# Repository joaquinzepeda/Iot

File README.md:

# Iot
Repositorio códigos curso Análisis y Diseño de Sistemas basados en Internet de las Cosas (IoT).

## Integrantes 
Ricardo Garcia, FCFM.  
Benjamín Irarrazabal, FCFM.  
Joaquín Zepeda, FCFM.  

# Diseño PCB

Se diseño la siguiente placa PCB para un sistema de regadio automático.

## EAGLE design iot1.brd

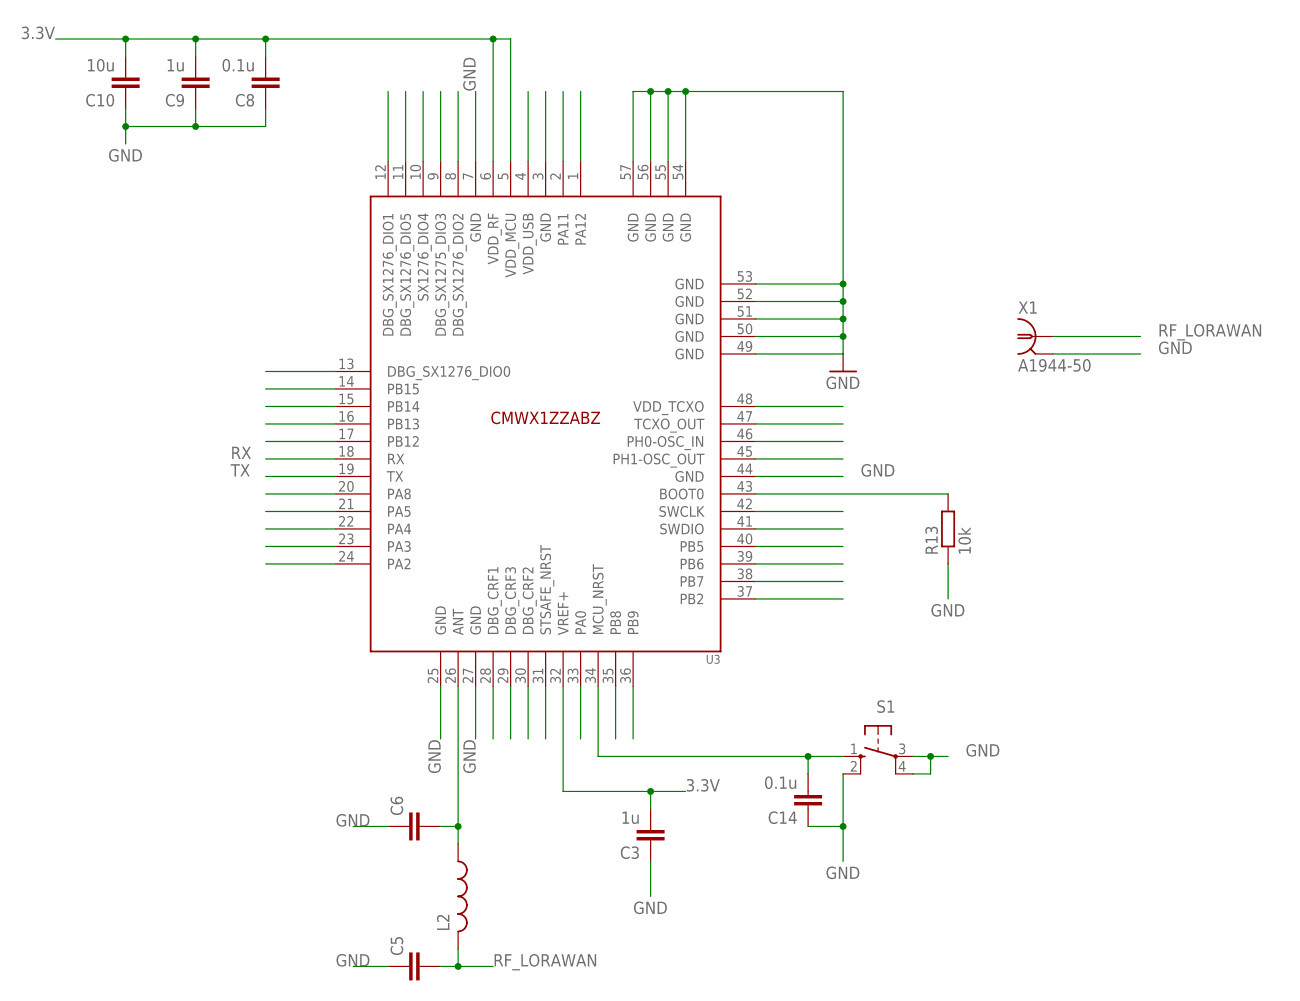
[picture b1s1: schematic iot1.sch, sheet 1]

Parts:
C3, C9: 1u; C050-025X075
C5, C6: C-EU050-025X075; C050-025X075
C8, C14: 0.1u; C050-025X075
C10: 10u; C050-025X075
L2: L-US0207/7; 0207/7
R13: 10k; 0204/5
S1: 10-XX; B3F-10XX
U3: CMWX1ZZABZ
X1: A1944-50; A1944

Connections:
3.3V: C3.2, C8.2, C9.2, C10.2, U3.5 (VDD_MCU), U3.6 (VDD_RF), U3.32 (VREF+); also elsewhere on the board
GND: C3.1, C5.1, C6.1, C8.1, C9.1, C10.1, C14.1, R13.1, S1.2 (S1), S1.3, S1.4 (P1), U3.7 (GND), U3.25 (GND), U3.27 (GND), U3.44 (GND), U3.49 (GND), U3.50 (GND), U3.51 (GND), U3.52 (GND), U3.53 (GND), U3.54 (GND), U3.55 (GND), U3.56 (GND), U3.57 (GND), X1.2, X1.3 (2), X1.4 (2), X1.5 (2); also elsewhere on the board
unnamed: C6.2, L2.1, U3.26 (ANT)
unnamed: C14.2, S1.1 (S), U3.34 (MCU_NRST)
unnamed: R13.2, U3.43 (BOOT0)
RF_LORAWAN: C5.2, L2.2, X1.1
RX: U3.18 (RX); also elsewhere on the board
TX: U3.19 (TX); also elsewhere on the board

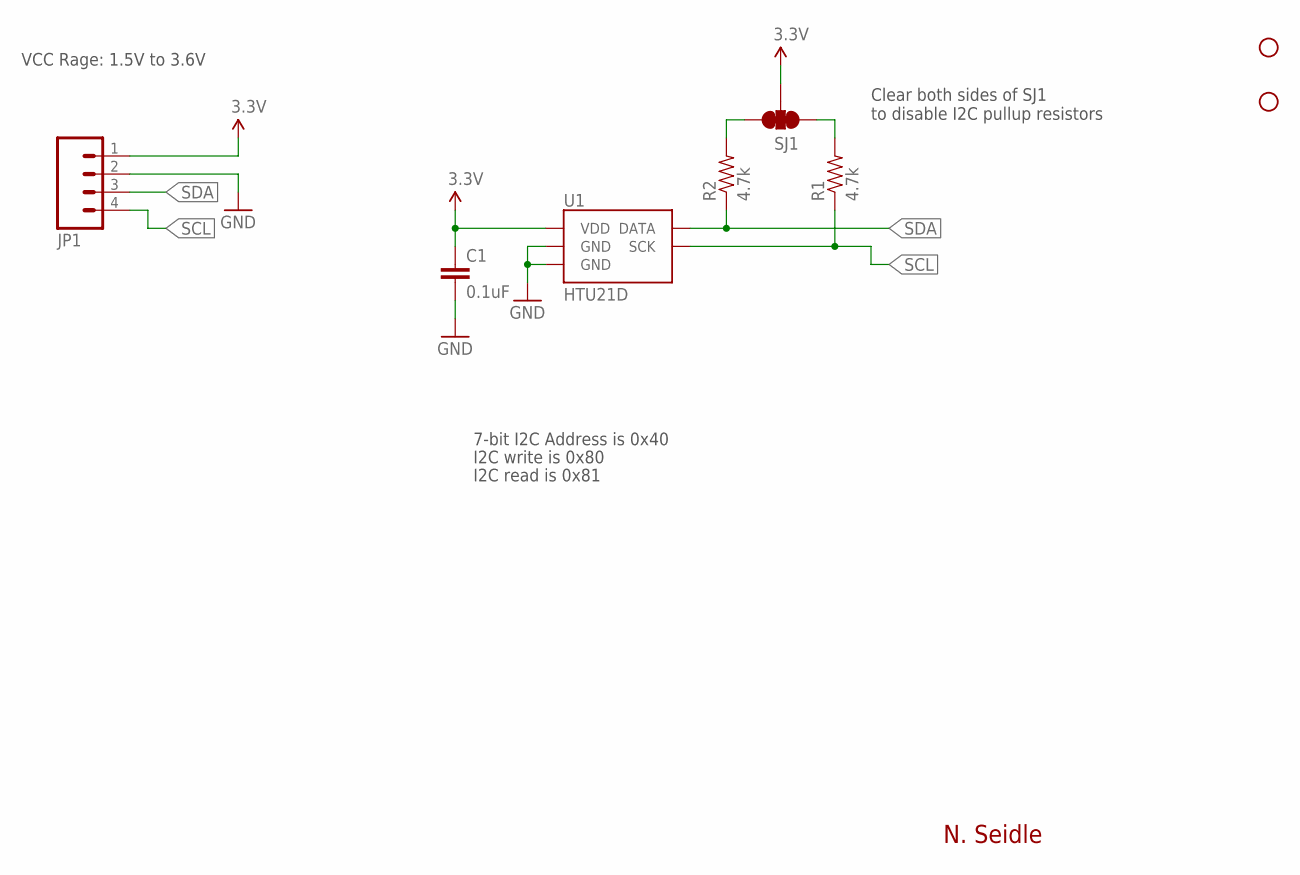
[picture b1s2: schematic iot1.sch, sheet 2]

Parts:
C1: 0.1uF; 0603-CAP
JP1: M04PTH; 1X04
R1, R2: 4.7k; 0603-RES
SJ1: SOLDERJUMPER_2WAYPASTE1&2&3; SJ_3_PASTE1&2&3
STANDOFF1, STANDOFF3: STAND-OFF
U1: HTU21D

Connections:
3.3V: C1.1, JP1.1, SJ1.2, U1.VDD; also elsewhere on the board
GND: C1.2, JP1.2, U1.7 (GND), U1.GND; also elsewhere on the board
unnamed: R2.2, SJ1.3
unnamed: R1.2, SJ1.1
SCL: JP1.4, R1.1, U1.SCK; also elsewhere on the board
SDA: JP1.3, R2.1, U1.DATA; also elsewhere on the board

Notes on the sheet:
N. Seidle
Clear both sides of SJ1 to disable I2C pullup resistors
VCC Rage: 1.5V to 3.6V
7-bit I2C Address is 0x40
I2C write is 0x80
I2C read is 0x81

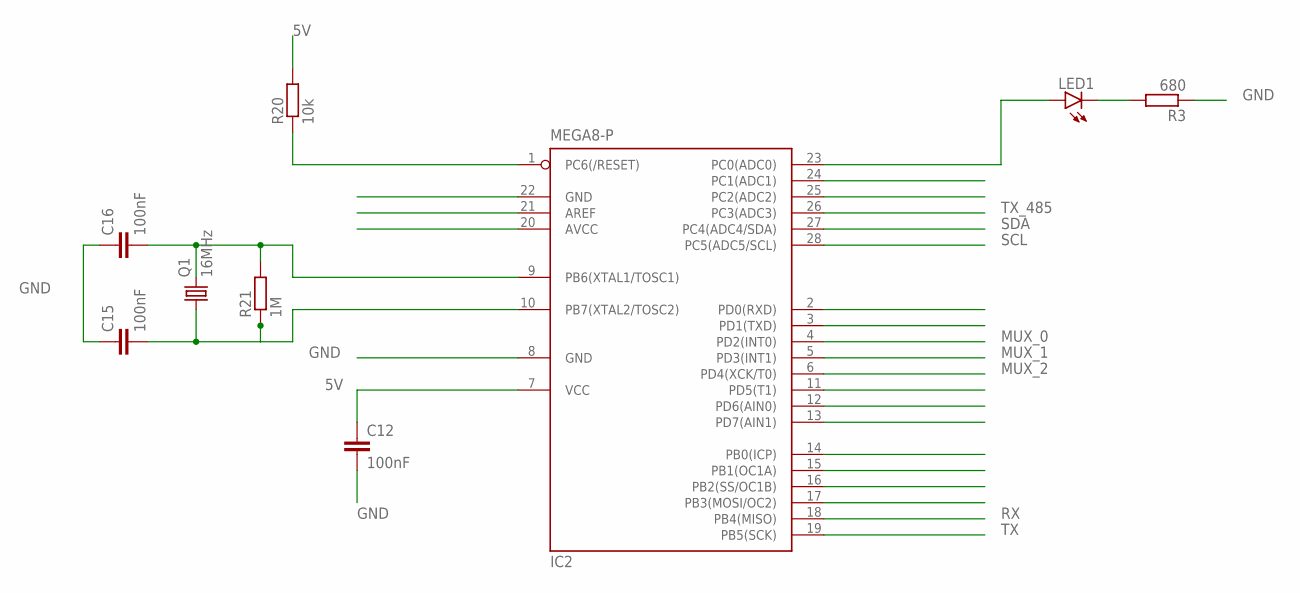
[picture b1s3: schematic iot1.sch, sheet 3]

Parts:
C12, C15, C16: 100nF; C050-025X075
IC2: MEGA8-P; DIL28-3
LED1: LED3MM
Q1: 16MHz; HC18U-V
R3: 680; 0207/10
R20: 10k; 0204/7
R21: 1M; 0204/7

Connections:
5V: C12.1, IC2.7 (VCC), R20.2; also elsewhere on the board
GND: C12.2, C15.1, C16.1, IC2.8 (GND), R3.1; also elsewhere on the board
MUX_0: IC2.4 (PD2(INT0)); also elsewhere on the board
MUX_1: IC2.5 (PD3(INT1)); also elsewhere on the board
MUX_2: IC2.6 (PD4(XCK/T0)); also elsewhere on the board
unnamed: IC2.23 (PC0(ADC0)), LED1.A
unnamed: IC2.1 (PC6(/RESET)), R20.1
unnamed: C15.2, IC2.10 (PB7(XTAL2/TOSC2)), Q1.1, R21.1
unnamed: C16.2, IC2.9 (PB6(XTAL1/TOSC1)), Q1.2, R21.2
unnamed: LED1.K (C), R3.2
RX: IC2.18 (PB4(MISO)); also elsewhere on the board
SCL: IC2.28 (PC5(ADC5/SCL)); also elsewhere on the board
SDA: IC2.27 (PC4(ADC4/SDA)); also elsewhere on the board
TX: IC2.19 (PB5(SCK)); also elsewhere on the board
TX_485: IC2.26 (PC3(ADC3)); also elsewhere on the board

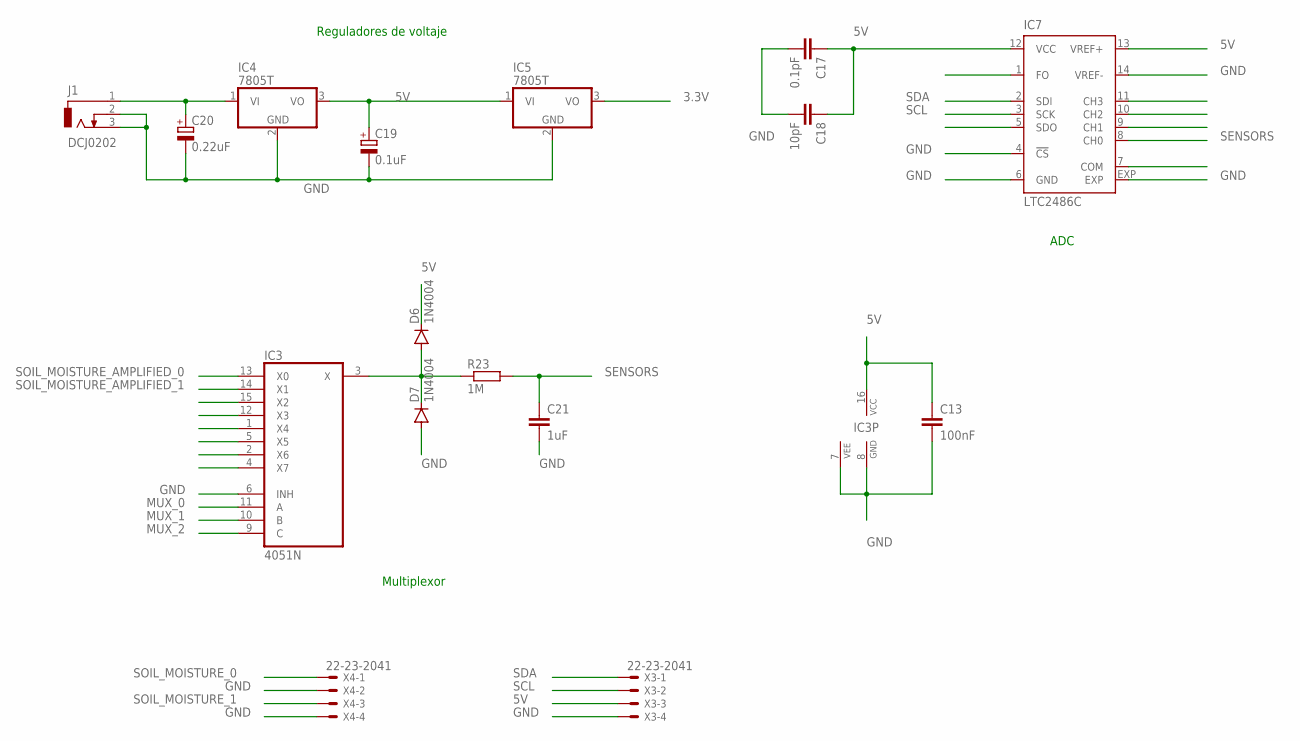
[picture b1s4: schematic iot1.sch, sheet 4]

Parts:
C13: 100nF; C0603
C17: 0.1pF; C0603
C18: 10pF; C0603
C19: 0.1uF; E1,8-4
C20: 0.22uF; E1,8-4
C21: 1uF; C0603
D6, D7: 1N4004; DO41-10
IC3: 4051N; DIL16
IC4, IC5: 7805T; TO220H
IC7: LTC2486C; DFN14-4X3
J1: DCJ0202
R23: 1M; 0207/10
X3, X4: 22-23-2041

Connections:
3.3V: IC5.3 (VO); also elsewhere on the board
5V: C13.1, C17.1, C18.1, C19.+, D6.C, IC3.16 (VCC), IC4.3 (VO), IC5.1 (VI), IC7.12 (VCC), IC7.13 (VREF+), X3.3; also elsewhere on the board
GND: C13.2, C17.2, C18.2, C19.-, C20.-, C21.2, D7.A, IC3.6 (INH), IC3.7 (VEE), IC3.8 (GND), IC4.2 (GND), IC5.2 (GND), IC7.4 (!CS), IC7.6 (GND), IC7.14 (VREF-), IC7.EXP, J1.2, J1.3, X3.4, X4.2, X4.4; also elsewhere on the board
MUX_0: IC3.11 (A); also elsewhere on the board
MUX_1: IC3.10 (B); also elsewhere on the board
MUX_2: IC3.9 (C); also elsewhere on the board
S: D6.A, D7.C, IC3.3 (X), R23.1
SCL: IC7.1 (FO), IC7.3 (SCK), X3.2; also elsewhere on the board
SDA: IC7.2 (SDI), X3.1; also elsewhere on the board
SENSORS: C21.1, IC7.8 (CH0), R23.2
SOIL_MOISTURE_0: X4.1; also elsewhere on the board
SOIL_MOISTURE_1: X4.3; also elsewhere on the board
SOIL_MOISTURE_AMPLIFIED_0: IC3.13 (X0); also elsewhere on the board
SOIL_MOISTURE_AMPLIFIED_1: IC3.14 (X1); also elsewhere on the board
V_IN: C20.+, IC4.1 (VI), J1.1

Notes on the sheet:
Multiplexor
ADC
Reguladores de voltaje

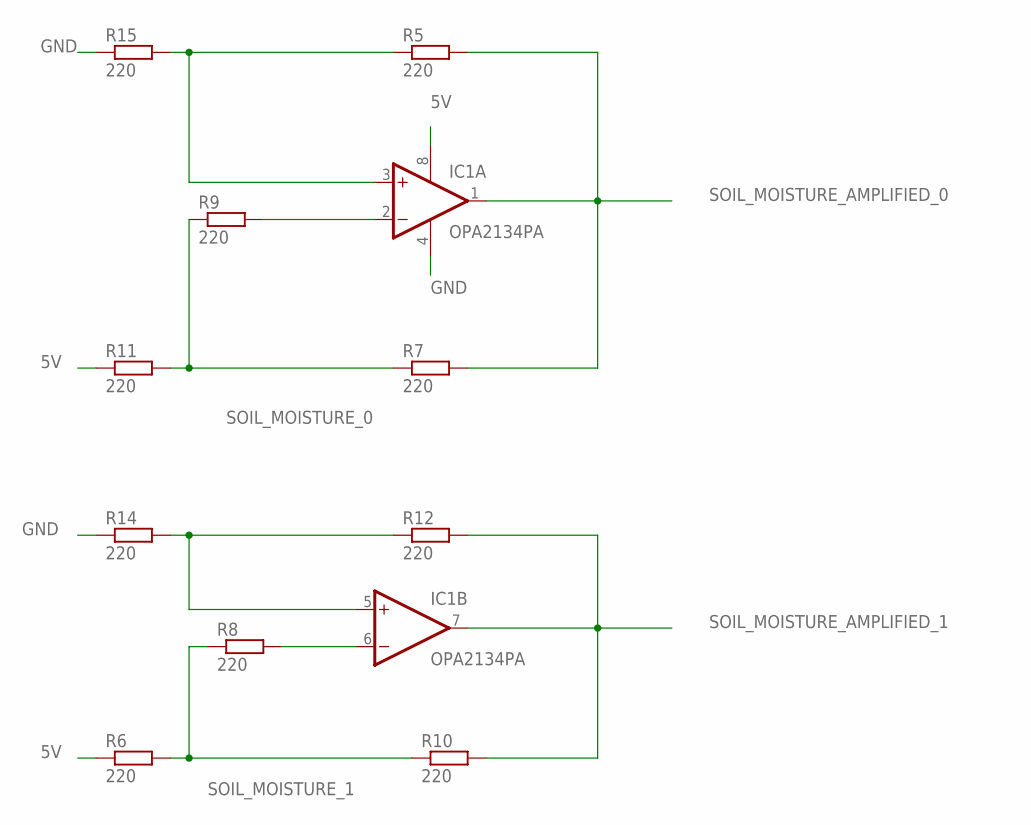
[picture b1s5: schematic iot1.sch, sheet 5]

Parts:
IC1: OPA2134PA; DIL08
R5, R6, R7, R8, R9, R10, R11, R12, R14, R15: 220; 0207/10

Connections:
5V: IC1.8 (V+), R6.1, R11.1; also elsewhere on the board
GND: IC1.4 (V-), R14.1, R15.1; also elsewhere on the board
unnamed: IC1.3 (+IN), R5.1, R15.2
unnamed: IC1.2 (-IN), R9.2
unnamed: IC1.5 (+IN), R12.1, R14.2
unnamed: IC1.6 (-IN), R8.2
SOIL_MOISTURE_0: R7.1, R9.1, R11.2; also elsewhere on the board
SOIL_MOISTURE_1: R6.2, R8.1, R10.1; also elsewhere on the board
SOIL_MOISTURE_AMPLIFIED_0: IC1.1 (OUT), R5.2, R7.2; also elsewhere on the board
SOIL_MOISTURE_AMPLIFIED_1: IC1.7 (OUT), R10.2, R12.2; also elsewhere on the board

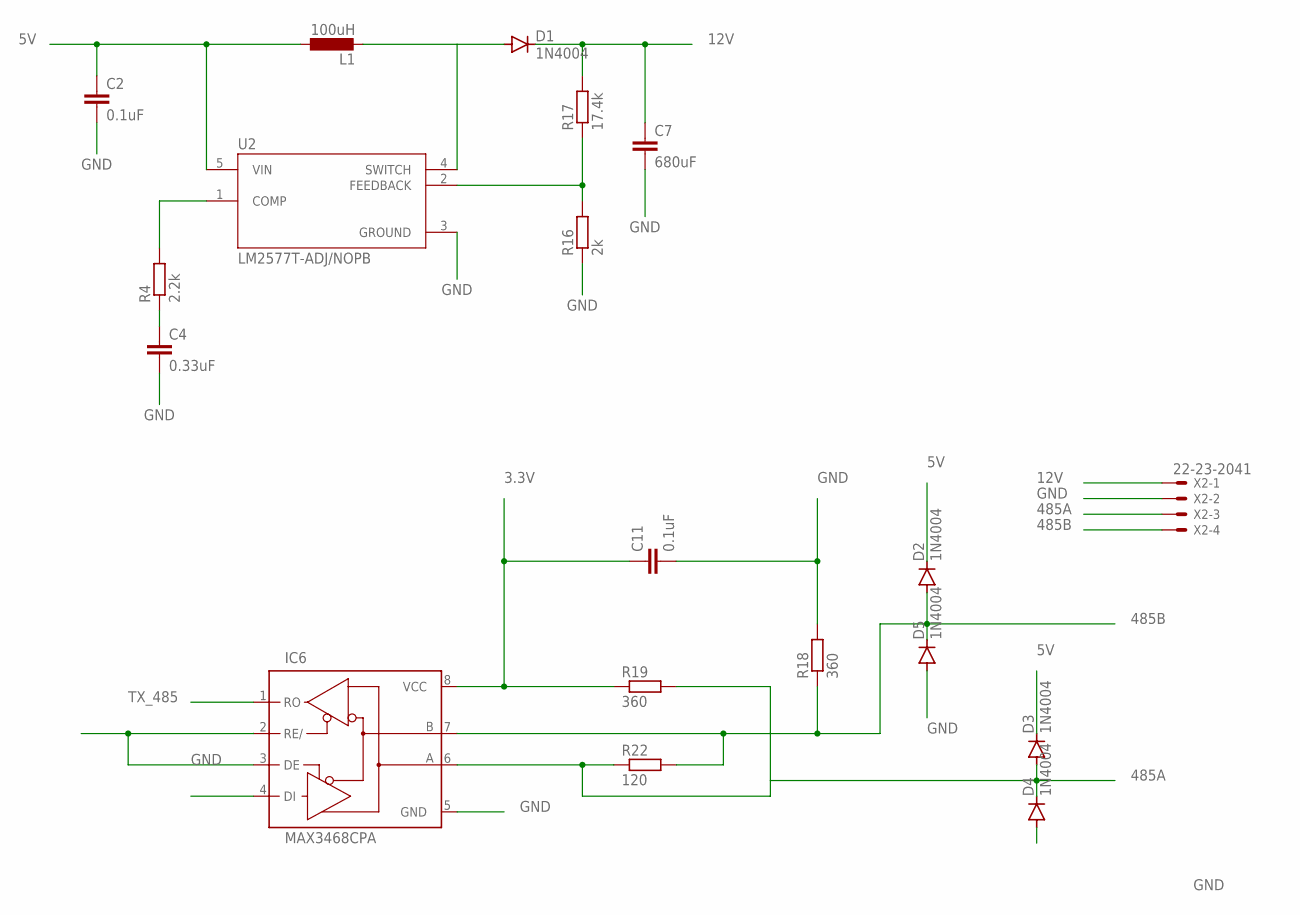
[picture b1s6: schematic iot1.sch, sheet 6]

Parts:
C2, C11: 0.1uF; C025-024X044
C4: 0.33uF; C025-024X044
C7: 680uF; C025-024X044
D1, D2, D3, D4, D5: 1N4004; DO41-10
IC6: MAX3468CPA; DIL08
L1: 100uH; L1812
R4: 2.2k; 0204/7
R16: 2k; 0204/7
R17: 17.4k; 0204/7
R18, R19: 360; 0207/10
R22: 120; 0207/10
U2: LM2577T-ADJ/NOPB; VREG_LM2577T-ADJ/NOPB
X2: 22-23-2041

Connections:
3.3V: C11.1, IC6.8 (VCC), R19.1; also elsewhere on the board
5V: C2.1, D2.C, D3.C, L1.1, U2.5 (VIN); also elsewhere on the board
12V: C7.1, D1.C, R17.2, X2.1
485A: D3.A, D4.C, IC6.6 (A), R19.2, R22.1, X2.3
485B: D2.A, D5.C, IC6.7 (B), R18.1, R22.2, X2.4
GND: C2.2, C4.2, C7.2, C11.2, D4.A, D5.A, IC6.2 (RE/), IC6.3 (DE), IC6.5 (GND), R16.1, R18.2, U2.3 (GROUND), X2.2; also elsewhere on the board
unnamed: D1.A, L1.2, U2.4 (SWITCH)
unnamed: R4.2, U2.1 (COMP)
unnamed: C4.1, R4.1
unnamed: R16.2, R17.1, U2.2 (FEEDBACK)
TX_485: IC6.1 (RO); also elsewhere on the board

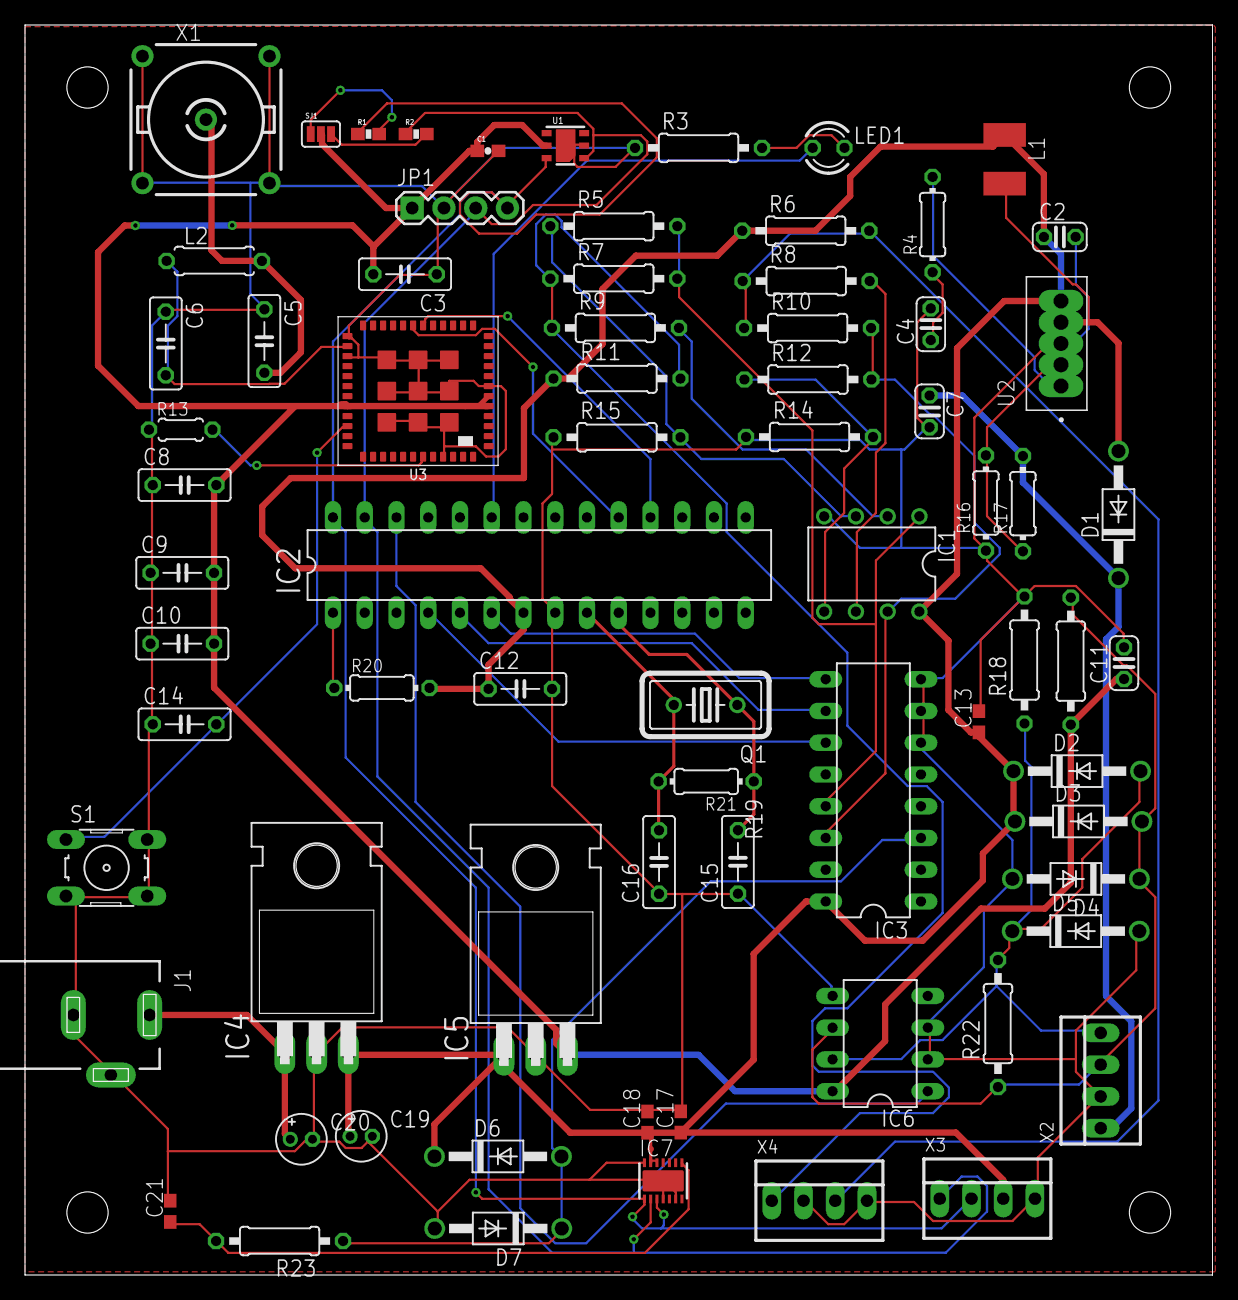
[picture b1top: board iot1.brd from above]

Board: 2 copper layers, 95.0 x 100.0 mm, 77 parts (0 on the bottom side), 40 nets.

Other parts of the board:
STANDOFF2, STANDOFF4: STAND-OFF

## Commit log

2023-05-28 esquematicos base
2023-05-31 adding MEGA8-P controller
2023-06-01 adding moisture input and adding voltage regulator
2023-06-01 adding power supply
2023-06-01 antena, power supply y conexiones lorawan
2023-06-03 3.3V regulator, multiplexer
2023-06-03 1Hz filter
2023-06-03 4-20ma amplification for soil moisture sensors
2023-06-03 rearranging items
2023-06-06 adding MAX485 module
2023-06-06 Step-up 5 to 12V
2023-06-06 Entrada Sensor de Temperatura y Humedad Ambiente
2023-06-06 adding MAX3468
2023-06-07 adding important wires
2023-06-07 all conections
2023-06-07 renumbering board components
2023-06-07 adding component's values
2023-06-07 fixing wiring errors
2023-06-07 adding gnds planes
2023-07-03 reorganizing folders
2023-07-03 creating check_connection_lora.ino
2023-07-03 programming check_connection_lora.ino
2023-07-03 commenting check_connection_lora.ino
2023-07-03 adding check ph and humidity ckecking connection script
2023-07-03 adding temperature ckecking connection script
2023-07-03 codigos maquinas de estado
2023-07-03 Máquinas de Lectura de Sensores
2023-07-03 updating files
2023-07-03 imagenes pcb

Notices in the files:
parts and their libraries:
SparkFun-Connectors: Licensing: CC v3.0 Share-Alike You are welcome to use this library for commercial purposes.
FaBo-LoRa: Released under the Creative Commons Attribution-ShareAlike 4.0 License
https://creativecommons.org/licenses/by-sa/4.0
